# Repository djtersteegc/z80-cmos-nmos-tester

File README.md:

Test your Z80 CPU at multiple frequencies and detemine if your remarked chip from China is a NMOS or CMOS variant. Based  on the work originally by [Виталий Рудик](https://oshwlab.com/vitalian1980/z80-tester) and later respun/improved by [kinzi](https://www.forum64.de/index.php?thread/133402-z80-tester-zum-testen-unbekannter-z80-cpus/).

I respun the PCB again to add a few quality of life improvements I wanted like a barrel power connetor, power switch and  LED, current measuring header, improved reset circuitry, and switched to 1/2 can oscillators instead of using a crystal and associated components (Pierce oscillator).

Unlike a simple NOP tester, this one works by loading a simple program from the EPROM/EEPROM.  It first checks the variant by using undocumented instructions like `OUT (C),0` , flashes the LED array one to three times to indicate the type, and then does a LED chaser display up and down the various data bus lines. Takes up to two 1/2 can oscillators and with the frequency dividers can test at the following frequencies. 

| Divider | 20 MHz Oscillator | 16 MHz Oscillator |
| ------- | ----------------- | ----------------- |
| Full    | 20 MHz            | 16 MHz            |
| 1/2     | 10 MHz            | 8 MHz             |
| 1/4     | 5 MHz             | 4 MHz             |
| 1/8     | 2.5 MHz           | 2 MHz             |
| 1/16    | 1.25 MHz          | 1 MHz             |

### BOM

There is an interactive BOM [here](https://djtersteegc.github.io/z80-cmos-nmos-tester/ibom.html) or [CSV](https://djtersteegc.github.io/z80-cmos-nmos-tester/z80-cmos-nmos-tester-BOM.csv).  I like using Winbond W27C512 EEPROM's in 27C512 applications since they don't require UV to erase like a traditional EPROM.

### Assembly

In the 3D directory there are STL's to print an (optional) LED alignment jig, some support blocks to keep the board level while you solder the LED's, and a simple mounting plate. Secure the PCB to the plate with M3 x 4mm screws.

### Firmware Programming

kinzi's rev3 firmare can be found in the zip file in the **firmware** directory.  Burn **test.z80.u880.rev3.bin** to a 27C512 compatible EPROM/EEPROM.

### Usage

Supply 5V center positive to the 5.5mm x 2.1mm DC power jack. On power up, the Z80 should automatically reset, if not, push the reset button.  The LED array will flash once for NMOS variants, twice for CMOS, or three times for a U880.  After that, the LED's will go "knight rider", and then reset in a continous loop.  Use the two jumpers to select the appropiate osciallator and frequency divider you want to test at.

JP1 (Current Test) feeds 5V to the Z80. Remove the jumper and attached a multimeter in current mode if you would like to test current draw of your Z80, another way to tell NMOS and CMOS variants apart. NMOS is around 200mA, CMOS is between 10 to 100mA depending on clock frequency.

Here's a quick demo of the board in action with both a real and fake 20MHz CMOS version from a batch of ten from AliExpress, https://youtu.be/2GuPsmFTtck

### Getting a PCB Board

Any extras I have available will be in my [Tindie](https://www.tindie.com/products/tersteeg/z80-cmos-nmos-tester-pcb/) store. I don't ship outside the US currently, but gerber files are available if you want to order your own from your favorite PCB fab like JLCPCB or PCBWay.

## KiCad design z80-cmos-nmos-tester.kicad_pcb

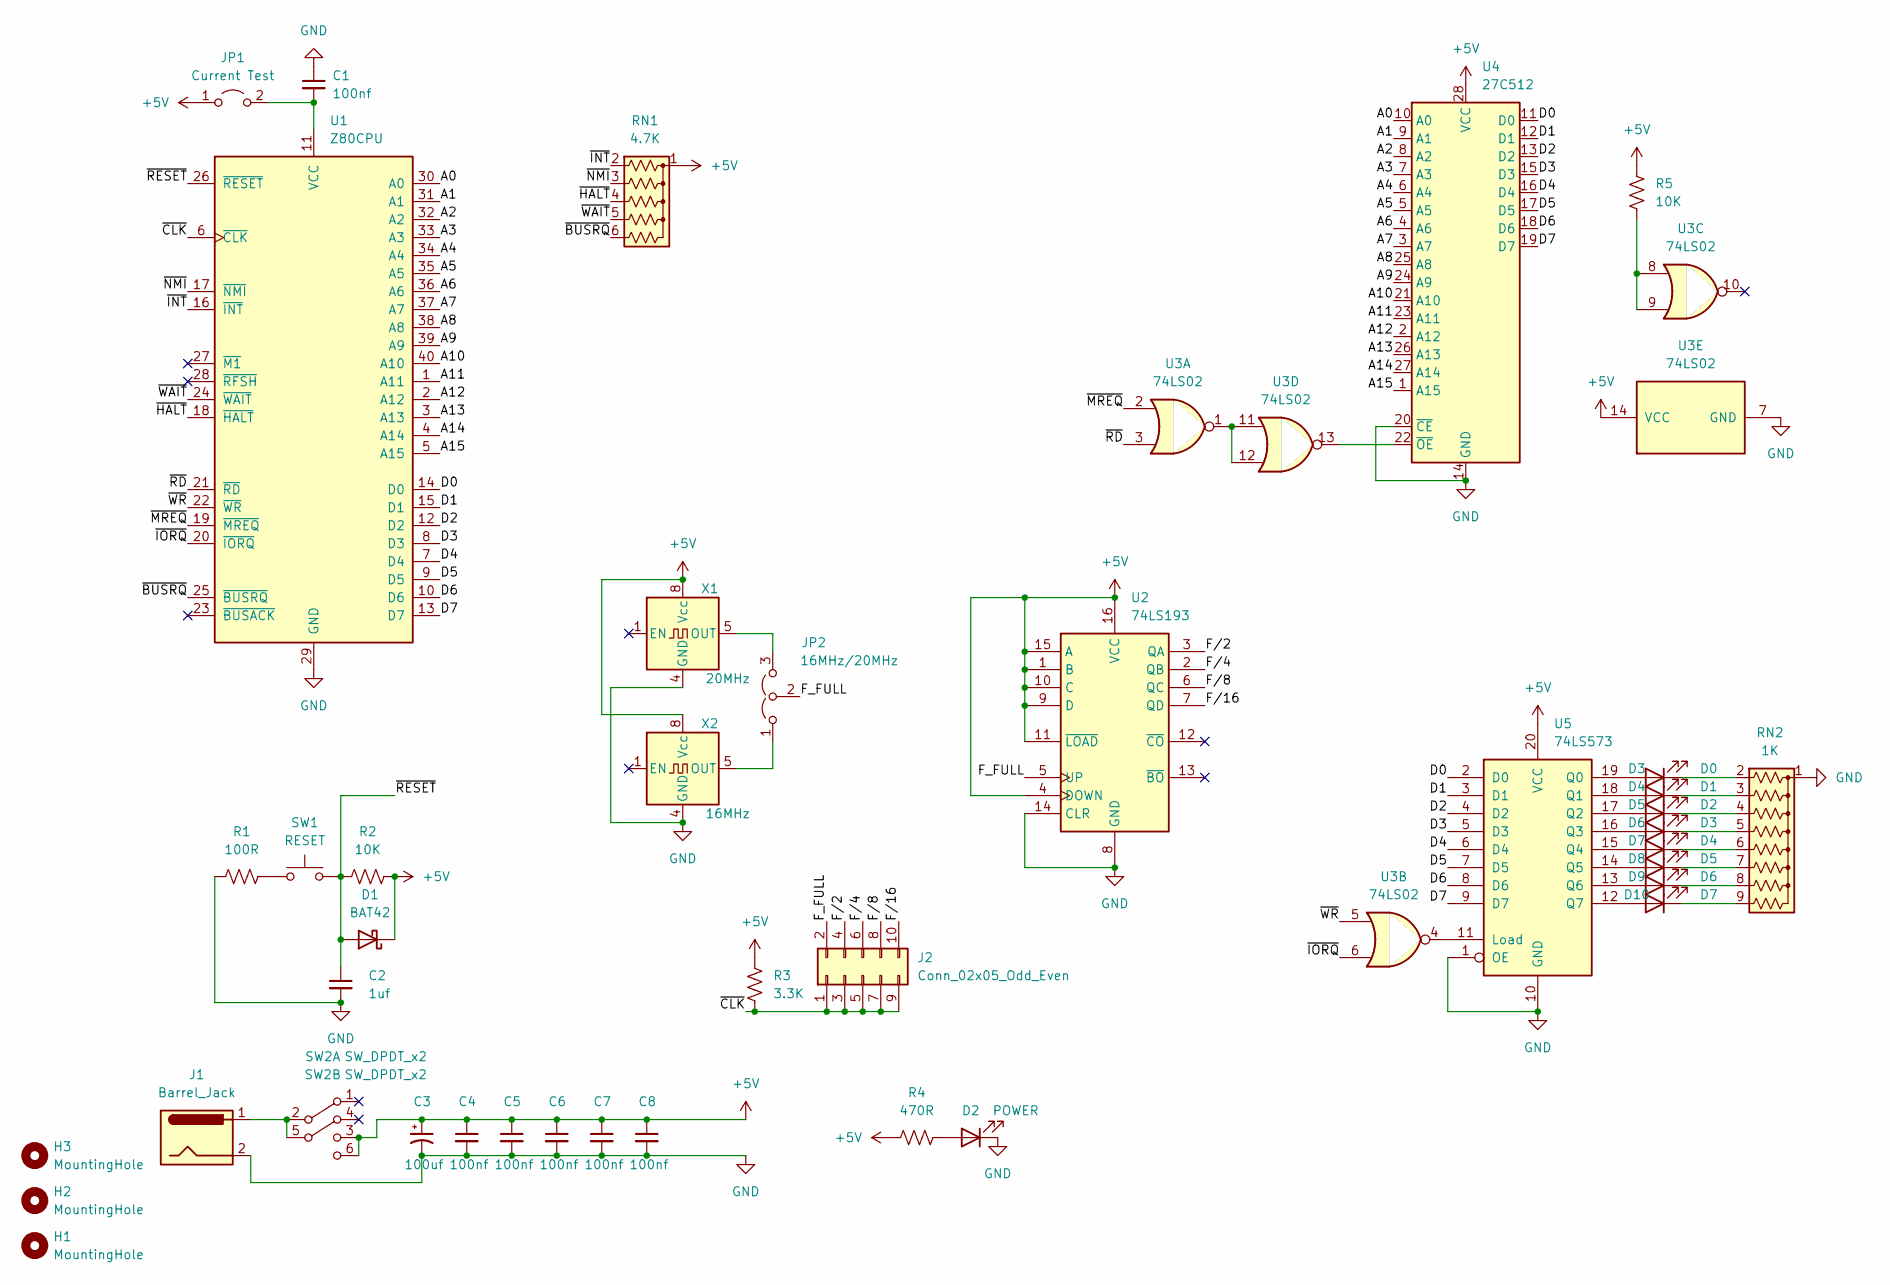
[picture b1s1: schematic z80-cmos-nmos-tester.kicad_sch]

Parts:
C1, C4, C5, C6, C7, C8: 100nf; C_Rect_L7.0mm_W3.5mm_P5.00mm
C2: 1uf; C_Rect_L7.0mm_W3.5mm_P5.00mm
C3: 100uf; CP_Radial_D5.0mm_P2.00mm
D1: BAT42; D_DO-35_SOD27_P7.62mm_Horizontal
D2: POWER; LED_D3.0mm
D3: D0; LED_D5.0mm
D4: D1; LED_D5.0mm
D5: D2; LED_D5.0mm
D6: D3; LED_D5.0mm
D7: D4; LED_D5.0mm
D8: D5; LED_D5.0mm
D9: D6; LED_D5.0mm
D10: D7; LED_D5.0mm
H1, H2, H3: MountingHole; MountingHole_3.2mm_M3
J1: Barrel_Jack; BarrelJack_Horizontal
J2: Conn_02x05_Odd_Even; PinHeader_2x05_P2.54mm_Vertical
JP1: Current Test; PinHeader_1x02_P2.54mm_Vertical
JP2: 16MHz/20MHz; PinHeader_1x03_P2.54mm_Vertical
R1: 100R; R_Axial_DIN0207_L6.3mm_D2.5mm_P7.62mm_Horizontal
R2: 10K; R_Axial_DIN0207_L6.3mm_D2.5mm_P7.62mm_Horizontal
R3: 3.3K; R_Axial_DIN0207_L6.3mm_D2.5mm_P7.62mm_Horizontal
R4: 470R; R_Axial_DIN0207_L6.3mm_D2.5mm_P7.62mm_Horizontal
R5: 10K; R_Axial_DIN0204_L3.6mm_D1.6mm_P5.08mm_Horizontal
RN1: 4.7K; R_Array_SIP6
RN2: 1K; R_Array_SIP9
SW1: RESET; SW_TH_Tactile_Omron_B3F-10xx
SW2: SW_DPDT_x2; KFC8.5x8.5 DPDT Push Switch
U1: Z80CPU; 3M_Textool_240-1288-00-0602J_2x20_P2.54mm
U2: 74LS193; DIP-16_W7.62mm_Socket_LongPads
U3: 74LS02; DIP-14_W7.62mm_Socket_LongPads
U4: 27C512; DIP-28_W15.24mm_Socket_LongPads
U5: 74LS573; DIP-20_W7.62mm_Socket_LongPads
X1: 20MHz; Oscillator_DIP-8
X2: 16MHz; Oscillator_DIP-8

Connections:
+5V: C3.1, C4.1, C5.1, C6.1, C7.1, C8.1, D1.1 (K), JP1.1 (A), R2.2, R3.2, R4.2, R5.2, RN1.1 (common), SW2.3 (C), SW2.6 (C), U2.1 (B), U2.4 (DOWN), U2.9 (D), U2.10 (C), U2.11 (~LOAD), U2.15 (A), U2.16 (VCC), U3.14 (VCC), U4.28 (VCC), U5.20 (VCC), X1.8 (Vcc), X2.8 (Vcc)
/A0: U1.30 (A0), U4.10 (A0)
/A1: U1.31 (A1), U4.9 (A1)
/A2: U1.32 (A2), U4.8 (A2)
/A3: U1.33 (A3), U4.7 (A3)
/A4: U1.34 (A4), U4.6 (A4)
/A5: U1.35 (A5), U4.5 (A5)
/A6: U1.36 (A6), U4.4 (A6)
/A7: U1.37 (A7), U4.3 (A7)
/A8: U1.38 (A8), U4.25 (A8)
/A9: U1.39 (A9), U4.24 (A9)
/A10: U1.40 (A10), U4.21 (A10)
/A11: U1.1 (A11), U4.23 (A11)
/A12: U1.2 (A12), U4.2 (A12)
/A13: U1.3 (A13), U4.26 (A13)
/A14: U1.4 (A14), U4.27 (A14)
/A15: U1.5 (A15), U4.1 (A15)
/D0: U1.14 (D0), U4.11 (D0), U5.2 (D0)
/D1: U1.15 (D1), U4.12 (D1), U5.3 (D1)
/D2: U1.12 (D2), U4.13 (D2), U5.4 (D2)
/D3: U1.8 (D3), U4.15 (D3), U5.5 (D3)
/D4: U1.7 (D4), U4.16 (D4), U5.6 (D4)
/D5: U1.9 (D5), U4.17 (D5), U5.7 (D5)
/D6: U1.10 (D6), U4.18 (D6), U5.8 (D6)
/D7: U1.13 (D7), U4.19 (D7), U5.9 (D7)
/F_FULL: J2.2, JP2.2 (C), U2.5 (UP)
/F/2: J2.4, U2.3 (QA)
/F/4: J2.6, U2.2 (QB)
/F/8: J2.8, U2.6 (QC)
/F/16: J2.10, U2.7 (QD)
/~BUSRQ: RN1.6 (R5), U1.25 (~BUSRQ)
/~CLK: J2.1, J2.3, J2.5, J2.7, J2.9, R3.1, U1.6 (~CLK)
/~HALT: RN1.4 (R3), U1.18 (~HALT)
/~INT: RN1.2 (R1), U1.16 (~INT)
/~IORQ: U1.20 (~IORQ), U3.6
/~MREQ: U1.19 (~MREQ), U3.2
/~NMI: RN1.3 (R2), U1.17 (~NMI)
/~RD: U1.21 (~RD), U3.3
/~RESET: C2.1, D1.2 (A), R2.1, SW1.2, U1.26 (~RESET)
/~WAIT: RN1.5 (R4), U1.24 (~WAIT)
/~WR: U1.22 (~WR), U3.5
GND: C1.1, C2.2, C3.2, C4.2, C5.2, C6.2, C7.2, C8.2, D2.1 (K), J1.2, R1.1, RN2.1 (common), U1.29 (GND), U2.8 (GND), U2.14 (CLR), U3.7 (GND), U4.14 (GND), U4.20 (~CE), U5.1 (OE), U5.10 (GND), X1.4 (GND), X2.4 (GND)
unnamed: D2.2 (A), R4.1
unnamed: D3.2 (A), U5.19 (Q0)
unnamed: D3.1 (K), RN2.2 (R1)
unnamed: D4.2 (A), U5.18 (Q1)
unnamed: D4.1 (K), RN2.3 (R2)
unnamed: D5.2 (A), U5.17 (Q2)
unnamed: D5.1 (K), RN2.4 (R3)
unnamed: D6.2 (A), U5.16 (Q3)
unnamed: D6.1 (K), RN2.5 (R4)
unnamed: D7.2 (A), U5.15 (Q4)
unnamed: D7.1 (K), RN2.6 (R5)
unnamed: D8.2 (A), U5.14 (Q5)
unnamed: D8.1 (K), RN2.7 (R6)
unnamed: D9.2 (A), U5.13 (Q6)
unnamed: D9.1 (K), RN2.8 (R7)
unnamed: D10.2 (A), U5.12 (Q7)
unnamed: D10.1 (K), RN2.9 (R8)
unnamed: C1.2, JP1.2 (B), U1.11 (VCC)
unnamed: JP2.1 (A), X2.5 (OUT)
unnamed: JP2.3 (B), X1.5 (OUT)
unnamed: R1.2, SW1.1
unnamed: R5.1, U3.8, U3.9
unnamed: J1.1, SW2.2 (B), SW2.5 (B)
unnamed: U3.1, U3.11, U3.12
unnamed: U3.13, U4.22 (~OE)
unnamed: U3.4, U5.11 (Load)

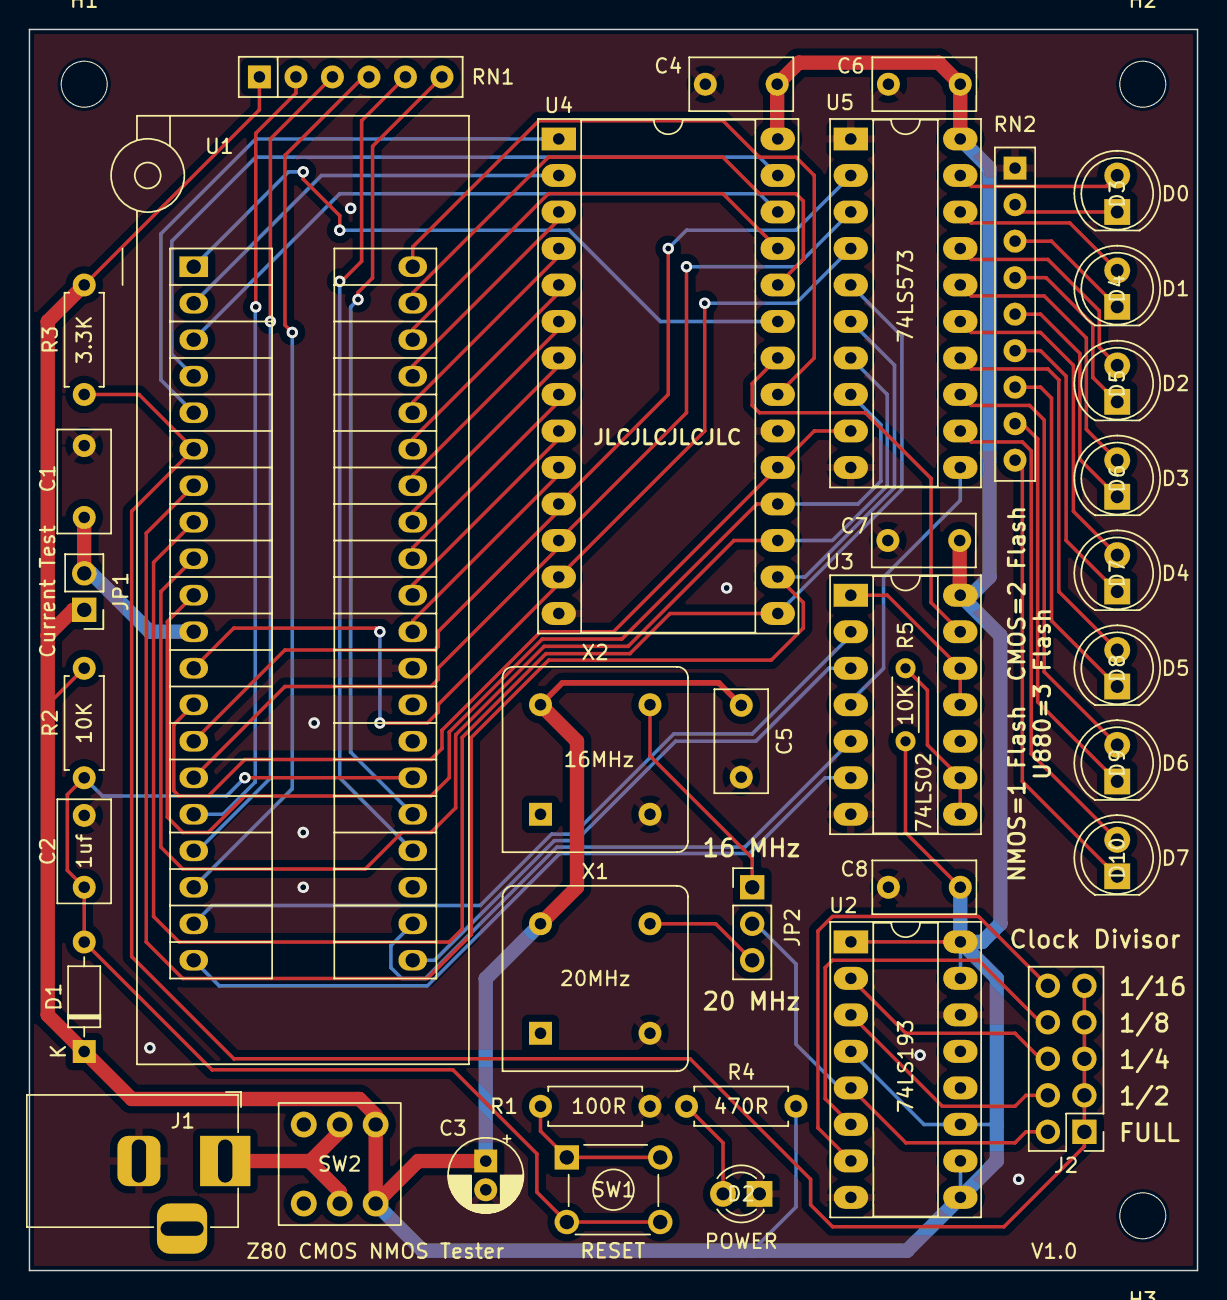
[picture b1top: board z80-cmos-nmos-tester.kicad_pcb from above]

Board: 2 copper layers, 81.3 x 86.4 mm, 41 parts (0 on the bottom side), 68 nets.

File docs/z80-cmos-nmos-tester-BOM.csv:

"#","Reference","Qty","Value","Footprint","DNP"
"1","C1, C4, C5, C6, C7, C8","6","100nf","Capacitor_THT:C_Rect_L7.0mm_W3.5mm_P5.00mm",""
"2","C2","1","1uf","Capacitor_THT:C_Rect_L7.0mm_W3.5mm_P5.00mm",""
"3","C3","1","100uf","Capacitor_THT:CP_Radial_D5.0mm_P2.00mm",""
"4","D1","1","BAT42","Diode_THT:D_DO-35_SOD27_P7.62mm_Horizontal",""
"5","D2","1","POWER","LED_THT:LED_D3.0mm",""
"6","D3","1","D0","LED_THT:LED_D5.0mm",""
"7","D4","1","D1","LED_THT:LED_D5.0mm",""
"8","D5","1","D2","LED_THT:LED_D5.0mm",""
"9","D6","1","D3","LED_THT:LED_D5.0mm",""
"10","D7","1","D4","LED_THT:LED_D5.0mm",""
"11","D8","1","D5","LED_THT:LED_D5.0mm",""
"12","D9","1","D6","LED_THT:LED_D5.0mm",""
"13","D10","1","D7","LED_THT:LED_D5.0mm",""
"14","H1, H2, H3","3","MountingHole","MountingHole:MountingHole_3.2mm_M3",""
"15","J1","1","Barrel_Jack","Connector_BarrelJack:BarrelJack_Horizontal",""
"16","J2","1","Conn_02x05_Odd_Even","Connector_PinHeader_2.54mm:PinHeader_2x05_P2.54mm_Vertical",""
"17","JP1","1","Current Test","Connector_PinHeader_2.54mm:PinHeader_1x02_P2.54mm_Vertical",""
"18","JP2","1","16MHz/20MHz","Connector_PinHeader_2.54mm:PinHeader_1x03_P2.54mm_Vertical",""
"19","R1","1","100R","Resistor_THT:R_Axial_DIN0207_L6.3mm_D2.5mm_P7.62mm_Horizontal",""
"20","R2","1","10K","Resistor_THT:R_Axial_DIN0207_L6.3mm_D2.5mm_P7.62mm_Horizontal",""
"21","R3","1","3.3K","Resistor_THT:R_Axial_DIN0207_L6.3mm_D2.5mm_P7.62mm_Horizontal",""
"22","R4","1","470R","Resistor_THT:R_Axial_DIN0207_L6.3mm_D2.5mm_P7.62mm_Horizontal",""
"23","R5","1","10K","Resistor_THT:R_Axial_DIN0204_L3.6mm_D1.6mm_P5.08mm_Horizontal",""
"24","RN1","1","4.7K","Resistor_THT:R_Array_SIP6",""
"25","RN2","1","1K","Resistor_THT:R_Array_SIP9",""
"26","SW1","1","RESET","Button_Switch_THT:SW_TH_Tactile_Omron_B3F-10xx",""
"27","SW2","1","SW_DPDT_x2","Tersteeg:KFC8.5x8.5 DPDT Push Switch",""
"28","U1","1","Z80CPU","Socket:3M_Textool_240-1288-00-0602J_2x20_P2.54mm",""
"29","U2","1","74LS193","Package_DIP:DIP-16_W7.62mm_Socket_LongPads",""
"30","U3","1","74LS02","Package_DIP:DIP-14_W7.62mm_Socket_LongPads",""
"31","U4","1","27C512","Package_DIP:DIP-28_W15.24mm_Socket_LongPads",""
"32","U5","1","74LS573","Package_DIP:DIP-20_W7.62mm_Socket_LongPads",""
"33","X1","1","20MHz","Oscillator:Oscillator_DIP-8",""
"34","X2","1","16MHz","Oscillator:Oscillator_DIP-8",""

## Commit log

2023-10-29 Initial version
2023-10-29 Add CSV BOM
2023-10-29 Update docs
2023-11-15 Add CSV BOM and PDF schematic
